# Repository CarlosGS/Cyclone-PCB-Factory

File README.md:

<p align="center">

<div align="center"><i>A 3D-printable (Rep-Rap alike) CNC machine, intended for PCB manufacture.</i></div>
</p>  

Read this, it's important!
-----------

Please note that this project is no longer active and is of historical interest only.
===========

Check out this thread before printing the parts: <https://github.com/CarlosGS/Cyclone-PCB-Factory/issues/57>

**Also take a look at the following locations:**

- **Releases: <https://github.com/carlosgs/Cyclone-PCB-Factory/releases>**
- **Documentation: <https://github.com/carlosgs/Cyclone-PCB-Factory/wiki>**

<p align="center">

<div align="center"><i>Cyclone v2. Picture by bq</i></div>
</p>

Mail list / Forum  
-------------------
If you are interested in this project, please consider joining our mail list:  
**English: <https://groups.google.com/forum/#!forum/cyclone-pcb-factory>**  
**Spanish/Español: <https://groups.google.com/forum/#!forum/cyclone-pcb-factory-es>**  

Links of interest  
====================
- **[GitHub project network](https://github.com/carlosgs/Cyclone-PCB-Factory/network)** (useful to find the latest work by collaborators)
- **[Wiki entry on RepRap.org](http://reprap.org/wiki/Cyclone_PCB_Factory)**
- **[Joco's Cyclone journey in the mail list](https://groups.google.com/forum/#!topic/cyclone-pcb-factory/o_YzXokpLnA)**
- **[A year of development (Jan/2014)](https://web.archive.org/web/20150627040708/http://carlosgs.es/node/47)** (project evolution during 2013)
- **[List of suppliers](https://github.com/carlosgs/Cyclone-PCB-Factory/wiki/List-of-suppliers)**

Getting the (development) source files  
========================================
Install git (http://git-scm.com/) onto your system. Then run a clone:

	git clone git://github.com/carlosgs/Cyclone-PCB-Factory.git

This will download the latest sources into a directory named 'Cyclone-PCB-Factory'.  

Current stable version: 2.1  
--  

**Recent news:**
* [Kris Wauters](http://www.digitalplayground.be/) has designed [a set of feet](http://www.thingiverse.com/thing:1131591) that raise up the machine and allow to place the electronics underneath. He has also made a [Z endstop support](http://www.thingiverse.com/thing:1131591). Check out his beautiful build in [his blog](http://www.digitalplayground.be/?p=3255).
* Introductory tutorial: [**Milling a bowl with bCNC**](https://github.com/carlosgs/grblForCyclone/wiki/2%29-Hello-World!-Mill-a-bowl-with-bCNC) (**implemented support for GRBL firmware in RAMPS and Sanguinololu** 3D printer electronics. GRBL is better for CNCs than Marlin).
* Released [**Cyclone XL (beta)**](Output_files/Cyclone_XL) with a milling area of **500x250mm**.
* BQ additions have been re-incorporated into the main parametric design (zip-ties in the Y carriage linear bearing holders, longer Z motor gear, same orientation for the Y rod idlers).
* If you use RAMPS, you may want to try this [GRBL mod](https://github.com/carlosgs/grblForCyclone), it is better than Marlin. Control it with the [bCNC](https://github.com/vlachoudis/bCNC) graphical interface.
* Z carriage modified for Dremel 3000 by [Nicolas Arias](https://groups.google.com/forum/#!msg/cyclone-pcb-factory/mfZC0KEy7gw/TaSLBKO9QJUJ) and [Marcos Bladauskas](https://groups.google.com/forum/#!msg/cyclone-pcb-factory/WJLWC5qAm-w/70eSQ2DBCAAJ) ([download it here](Output_files/Zcarriages)).
* Check out the [Arduino CNC shield housing](http://www.thingiverse.com/thing:929981) by Oliver Kreuzenbeck (Helicon).
* [Source code improvements (better parameterization, M4 screw version)](https://github.com/carlosgs/Cyclone-PCB-Factory/pull/33) by [Arne Durr (D-Byte)](https://github.com/D-Byte).
* An [**aluminium spindle holder**](https://github.com/carlosgs/Cyclone-PCB-Factory/pull/40) by [Marc Muntada (quikshot)](https://github.com/quikshot) ([download it here](Output_files/Zcarriages)).
* There is also [a folder](bq_additions) with the version by [Pedro de Oro](https://github.com/PedroDeOro) and [Luis Díaz](http://diwo.bq.com/author/ldiaz/) from **bq**, with some additions that simplify the assembly process (these have already been merged into the main branch).
* Daniel Evrard has [assembled Cyclone in Sketchup](https://groups.google.com/forum/#!msg/cyclone-pcb-factory/1TpFxE7avRo/EBSx7ouy9GwJ) which can be very useful as a template.
* Thanks must also go to [ve3sjk](https://github.com/ve3sjk), [joco-nz](https://github.com/joco-nz), Aisflow, Yiannis Mandravellos, Samuel Kranz and [yOPERO](https://github.com/yOPERO) for their constructive discussions and continuous support.
* If your printer is too small to print the main frames of the machine, take a look at the [**shorter version of the frames**](Output_files/ShorterVersion) (thanks [Burt Bicksler!!](https://groups.google.com/forum/#!msg/cyclone-pcb-factory/ue6NiWs713w/A7_4h4Ynf54J)).

**Cyclone PCB Factory V2.0 was developed in the department of innovation and robotics at [bq](http://www.bq.com/)**  
**V2.0** addressed all the issues from the original design, and implementing improvements by yOPERO, Martin Zabojnik and others:  

* More robust design with tougher parts:
 * Better holders for the linear bearings (vibration made them slide away)
 * Reinforced nut/screw holders
* Anti-backlash mechanisms
* Improved gears with smoother edges
* Protective cover for the gears
* Attachment for a vacuum cleaner
* Better scalability (parameterized design)
* Using a [Dremel 200](http://www.dremel.com/en-us/tools/Pages/ToolDetail.aspx?pid=200+Series) as the spindle motor
* Integrated endstop holders

<p align="center">

<div align="center"><i>Render of Cyclone v2.0</i></div>
</p>  

<p align="center">

<div align="center"><i>The new design tries to be more parameterized</i></div>
</p>

Videos  
--  
- October 2015. Full milling process with bCNC, by Carlosgs: <https://www.youtube.com/watch?v=tWrt1B1CeP0>
- September 2015. Cyclone PCB jogging and homing test with bCNC, by Ianmcmill: <https://www.youtube.com/watch?v=GqbSjCq_hWg>
- July 2015. v2.0 Milling a PCB, timelapse by Helicon007: <https://www.youtube.com/watch?v=GpFG2Z8Jt-w>
- April 2015. Cyclone PCB Factory belt drive, by Nihilianth: <https://www.youtube.com/watch?v=bdu1vz6ndGs>
- April 2015. Introduction & assembly tips, by Project23D: <https://www.youtube.com/watch?v=0mW087ijIdE>
- v2.0 Plexiglass "Open Source Hardware" keychain: <http://www.youtube.com/watch?v=3Kftgog89wQ>
- v2.0 Cyclone Logo in PCB (October 2014): <http://www.youtube.com/watch?v=_6oWuco_N8U>
- v2.0a Plexiglass Cyclone logo (August 2014): <http://www.youtube.com/watch?v=lPQlIvBf7Ak>
- v2.0a Milling wax (August 2014): <http://www.youtube.com/watch?v=drV_r_OSsi4>
- February 2014. First drawing test with the Cyclone PCB Factory CNC, by Samuel Ureta: <https://www.youtube.com/watch?v=F7SczbShmxA>
- December 2013. Adjustment of Cyclone PCB Factory Y Stepper Motor Current, by Glen Chung: <https://www.youtube.com/watch?v=-TPqWOsY0Ls>
- v0.9.7 Cyclone PCB factory, the process (June 2013): <http://www.youtube.com/watch?v=fKW3fwy1h0k>
- v0.9.6 Y axis concept by yOPERO <http://www.youtube.com/watch?v=XzcobonQP40>
- v0.9.5 Probing a PCB <http://www.youtube.com/watch?v=m5zXL8k5T9E>
- v0.9.5 Milling MDF <http://www.youtube.com/watch?v=2QpxjheEjEc> and <http://www.youtube.com/watch?v=zjav0hBtmYA>
- v0.8 Drawing test: <http://www.youtube.com/watch?v=Y-HSdE89JOM>
- v0.7.5 XY axis test: <http://www.youtube.com/watch?v=9umlq4oHG64>
- v0.7.5 High speed XY test: <http://www.youtube.com/watch?v=H3uYCXryj60>

- October 2015. Evolution of the Cyclone-PCB-Factory GitHub repository (Gource Visualization), by Landon Wilkins: <https://www.youtube.com/watch?v=0ANaGCHkaco>

More pictures  
--  

License  
--
License: **Attribution - Share Alike - Creative Commons (<http://creativecommons.org/licenses/by-sa/3.0/>)**  

Authors:  
--
**Carlos García Saura (<http://github.com/CarlosGS>)** released the project as open-source and is the current maintainer.

**Many other people keeps contributing to the project (check GitHub contributions and "most active posters" at <https://groups.google.com/forum/#!aboutgroup/cyclone-pcb-factory>).**  

Special thanks  
--  
- **Arne Durr (D-Byte)** finished the OpenScad assembly and made the code much more parametric.  
- Plenty of feedback from **Pedro de Oro**, **Alberto Valero**, **Alberto Mendez** (and **Obijuan**, **Pacle**, **Jesus**, **Ana**, **Santi**, **Antonio**, **Jose**... :-P) at the _department of innovation and robotics at [bq](http://www.bq.com/)_. **Cyclone is much more user-friendly thanks to you!**  
- **Glen Chung** (<https://github.com/glenchung>) improved the OpenScad code quite a lot (a much more elegant code), providing a great start point for V2.0.  
- Z axis concepts by **Quim Borras** and the spindle motor holder by **Misan** were really useful!! Also, **Diego Viejo**'s machine was of great inspiration for the Z axis (<https://plus.google.com/u/0/photos/113930344830086538817/albums/5868944432651911713?authkey=CLDJgdehlN773gE>) **Thank you all!!**  
- This design woudn't have been possible without the encouragement of the **Panda CNC community** (<https://plus.google.com/u/0/communities/102402711800402614517>)  
- Also, thanks to **Juan González-Gómez (Obijuan <http://iearobotics.com>)** for naming the machine Cyclone :)  

Derived from / we have used / inspirational  
--
- "Linear actuator concept for CNC machines" by **Carlosgs** (<http://www.thingiverse.com/thing:45103>)  
- "Obiscad library" by **Obijuan** (<https://github.com/Obijuan/obiscad>)  
- "Minimal footprint friction-fit LM8UU holder" by **thantik** (<http://www.thingiverse.com/thing:23041>)  
- "Spindle mount for ShapeOko" by **Misan** (<http://www.thingiverse.com/thing:26740>)  
- "Carro Z para Cyclone CNC mill intended for PCB" by **Quim** (<http://www.thingiverse.com/thing:80718>)  
- "Write.scad (and DXF fonts)" by **HarlanDMii** (<http://www.thingiverse.com/thing:16193>)  
- "PCB Machining Vise" by **Forgetful_Guy** (<http://www.thingiverse.com/thing:63578>)  

Credit for the ideas used  
--  
The origin of Cyclone took place while I (carlosgs) was inside the **Panda CNC** community (<https://plus.google.com/u/0/communities/102402711800402614517>). This is from December 2012 to mid-February 2013.  
Here is the credit for the ideas that were used:  

* _Let's design a 3D-printable CNC for PCB milling, it will be named Panda:_ **Guillermo Welch** (mid-December, via Google Talk)  
* _X carriage rod distribution:_ **César Augusto Fernández Cano** claims Cyclone's X axis is a derivate of his concept: <https://plus.google.com/u/0/111421387442355054591/posts/QrfYtEuZBaj>  
* _100x160mm workspace:_ **David Martin** <https://dl.dropboxusercontent.com/u/16122275/PandaCNC_credit/workplace_size.png>  
* _Using gears to drive the X-Y axes:_ **Guillermo Welch** <https://plus.google.com/u/0/101232926728463427403/posts/QjZGNcWcgGg>  
* _Regarding the woodbase:_ **Guillermo Welch** always contemplated the possibility of attaching the machine (optionally) to a woodbase. I decided to use the base as a main structural part instead. See <https://dl.dropboxusercontent.com/u/16122275/PandaCNC_credit/woodbase.png> (screenshot from <https://plus.google.com/u/0/113437723819360223498/posts/8LDCSSVWqCS>)  
* _List of CNC endmill types:_ **David Martin** <https://dl.dropboxusercontent.com/u/16122275/PandaCNC_credit/cnc_endmill_types.png>  

Please note I have taken screenshots of the post that are on the closed G+ Panda community (<https://plus.google.com/u/0/communities/116318709564872967169>). You can register and see by yourself.  

**All other development present on Cyclone has nothing to do with Panda and is not related to the Panda project.**  

Disclaimer  
--
This hardware/software is provided "as is", and you use the hardware/software at your own risk. Under no circumstances shall any author be liable for direct, indirect, special, incidental, or consequential damages resulting from the use, misuse, or inability to use this hardware/software, even if the authors have been advised of the possibility of such damages.  

Please cite as:
--
Garcia-Saura, C. (2013). Cyclone PCB Factory. GitHub. https://doi.org/10.5281/ZENODO.10442930

Latex / Bibtex citation:
```bibtex
@misc{cyclonepcb2013,
  author = {Garcia-Saura, Carlos},
  title = {Cyclone PCB Factory},
  publisher = {GitHub},
  year = {2013},
  doi = {10.5281/ZENODO.10442930},
  url = {https://doi.org/10.5281/ZENODO.10442930}
}
```

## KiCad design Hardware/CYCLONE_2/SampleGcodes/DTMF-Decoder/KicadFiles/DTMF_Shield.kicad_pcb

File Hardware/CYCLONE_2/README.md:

A 3D-printable (Rep-Rap alike) CNC machine, intended for PCB manufacture.  

Read this, it's important!
===========================
If you are reading this, then you are looking at the development version of Cyclone PCB Factory.
This means files may present inconsistencies (dimensions mismatch, lack of tolerances, etc).
If you just want to build the machine, take a look at the following locations:

- **Releases: <https://github.com/carlosgs/Cyclone-PCB-Factory/releases>**
- **Documentation: <http://reprap.org/wiki/Cyclone_PCB_Factory>**

<p align="center">

<div align="center"><i>Cyclone v2.0</i></div>
</p>

Mail list / Forum  
-------------------
If you are interested in this project, please consider joining our mail list:  
**<https://groups.google.com/forum/#!forum/cyclone-pcb-factory>**  
Any help and feedback will be appreciated, particularly with software usage and software development :)  

Links of interest  
====================
- **[Project network](https://github.com/carlosgs/Cyclone-PCB-Factory/network)** (useful to find the latest work by collaborators)
- **[Wiki entry on RepRap.org](http://reprap.org/wiki/Cyclone_PCB_Factory)**
- **[A year of development (01/20/2014)](http://carlosgs.es/node/47)** (with information regarding the evolution of the project in 2013)

Getting the (development) source files  
========================================
Install git (http://git-scm.com/) onto your system. Then run a clone:

	git clone git://github.com/carlosgs/Cyclone-PCB-Factory.git

This will download the latest sources into a directory named 'Cyclone-PCB-Factory'.  

Version 2.0  
--  

**Cyclone PCB Factory V2.0 was developed in the department of innovation and robotics at [bq](http://www.bq.com/)**  

V2.0 addresses all the issues from the original design, and implementing improvements by yOPERO, Martin Zabojnik and others.  

* More robust design with tougher parts:
 * Better holders for the linear bearings (vibration made them slide away)
 * Reinforced nut/screw holders
* Anti-backlash mechanisms
* Improved gears with smoother edges
* Protective cover for the gears
* Attachment for a vacuum cleaner
* Better scalability (parametrized design)
* Using a [Dremel 200](http://www.dremel.com/en-us/tools/Pages/ToolDetail.aspx?pid=200+Series) as the spindle motor
* Integrated endstop holders

Future improvements:  
--  
* Endstop integration for Z (integrated probe)
* Re-implement the Z carriage, currently inherited from Cyclone V1

Videos  
--  
- v2.0 Plexiglass "Open Source Hardware" keychain: <http://www.youtube.com/watch?v=3Kftgog89wQ>
- v2.0 Cyclone Logo in PCB (October 2014): <http://www.youtube.com/watch?v=_6oWuco_N8U>
- v2.0a Plexiglass Cyclone logo (August 2014): <http://www.youtube.com/watch?v=lPQlIvBf7Ak>
- v2.0a Milling wax (August 2014): <http://www.youtube.com/watch?v=drV_r_OSsi4>
- v0.9.7 Cyclone PCB factory, the process (June 2013): <http://www.youtube.com/watch?v=fKW3fwy1h0k>
- v0.9.6 Y axis concept by Yopero <http://www.youtube.com/watch?v=XzcobonQP40>  
- v0.9.5 Probing a PCB <http://www.youtube.com/watch?v=m5zXL8k5T9E>  
- v0.9.5 Milling MDF <http://www.youtube.com/watch?v=2QpxjheEjEc> and <http://www.youtube.com/watch?v=zjav0hBtmYA>  
- v0.8 Drawing test: <http://www.youtube.com/watch?v=Y-HSdE89JOM>  
- v0.7.5 XY axis test: <http://www.youtube.com/watch?v=9umlq4oHG64>  
- v0.7.5 High speed XY test: <http://www.youtube.com/watch?v=H3uYCXryj60>  

Bill of materials (obsolete, to be updated and moved to the RepRap wiki page)  
--  
Kobus' <https://docs.google.com/spreadsheet/ccc?key=0AjYcEd1WlkqCdERINEFvRk9mVTZvdXZFR0VHVjRWc2c#gid=0>  
Robsbots' <https://docs.google.com/spreadsheet/ccc?key=0AmiiQRLnjs9cdE12VDFmTHJ4N3JoTzcwbkJPb0ZLSWc#gid=0>  
Carlosgs' <https://docs.google.com/spreadsheet/ccc?key=0AsQp8IK25R4IdGk3LTdOWmpFR0Nrc0RhaVJaUC1CMUE>  

<p align="center">

<div align="center"><i>Render of Cyclone v2.0</i></div>
</p>  

<p align="center">

<div align="center"><i>The new design tries to be more parametrized</i></div>
</p>

License  
--
License: **Attribution - Share Alike - Creative Commons (<http://creativecommons.org/licenses/by-sa/3.0/>)**  

Authors:  
--
Carlos García Saura (Carlosgs <http://carlosgs.es>) is the original author of V2.0.  
Many other people keeps contributing to the project (check "most active posters" at <https://groups.google.com/forum/#!aboutgroup/cyclone-pcb-factory>).  

Special thanks  
--  
- Plenty of feedback from **Pedro de Oro**, **Alberto Valero**, **Alberto Mendez** (and **Obijuan**, **Pacle**, **Jesus**, **Ana**, **Santi**, **Antonio**, **Jose**... :-P) at the _department of innovation and robotics at [bq](http://www.bq.com/)_. **Cyclone is much more user-friendly thanks to you!**
- Z axis concepts by **Quim Borras** and the spindle motor holder by **Misan** were really useful!! Also, **Diego Viejo**'s machine was of great inspiration for the Z axis (<https://plus.google.com/u/0/photos/113930344830086538817/albums/5868944432651911713?authkey=CLDJgdehlN773gE>) **Thank you all!!**  
- This design woudn't have been possible without the encouragement of the **Panda CNC community** (<https://plus.google.com/u/0/communities/102402711800402614517>)  
- Also, thanks to **Juan González-Gómez (Obijuan <http://iearobotics.com>)** for naming the machine Cyclone :)  

Derived from / we have used / inspirational  
--
- "Linear actuator concept for CNC machines" by **Carlosgs** (<http://www.thingiverse.com/thing:45103>)  
- "Obiscad library" by **Obijuan** (<https://github.com/Obijuan/obiscad>)  
- "Minimal footprint friction-fit LM8UU holder" by **thantik** (<http://www.thingiverse.com/thing:23041>)  
- "Spindle mount for ShapeOko" by **Misan** (<http://www.thingiverse.com/thing:26740>)  
- "Carro Z para Cyclone CNC mill intended for PCB" by **Quim** (<http://www.thingiverse.com/thing:80718>)  
- "Write.scad (and DXF fonts)" by **HarlanDMii** (<http://www.thingiverse.com/thing:16193>)  
- "PCB Machining Vise" by **Forgetful_Guy** (<http://www.thingiverse.com/thing:63578>)  

Credit for the ideas used  
--  
The origin of Cyclone took place while I (carlosgs) was inside the **Panda CNC** community (<https://plus.google.com/u/0/communities/102402711800402614517>). This is from December 2012 to mid-February 2013.  
Here is the credit for the ideas that were used:  

* _Let's design a 3D-printable CNC for PCB milling, it will be named Panda:_ **Guillermo Welch** (mid-December, via Google Talk)  
* _X carriage rod distribution:_ **César Augusto Fernández Cano** claims Cyclone's X axis is a derivate of his concept: <https://plus.google.com/u/0/111421387442355054591/posts/QrfYtEuZBaj>  
* _100x160mm workspace:_ **David Martin** <https://dl.dropboxusercontent.com/u/16122275/PandaCNC_credit/workplace_size.png>  
* _Using gears to drive the X-Y axes:_ **Guillermo Welch** <https://plus.google.com/u/0/101232926728463427403/posts/QjZGNcWcgGg>  
* _Regarding the woodbase:_ **Guillermo Welch** always contemplated the possibility of attaching the machine (optionally) to a woodbase. I decided to use the base as a main structural part instead. See <https://dl.dropboxusercontent.com/u/16122275/PandaCNC_credit/woodbase.png> (screenshot from <https://plus.google.com/u/0/113437723819360223498/posts/8LDCSSVWqCS>)  
* _List of CNC endmill types:_ **David Martin** <https://dl.dropboxusercontent.com/u/16122275/PandaCNC_credit/cnc_endmill_types.png>  

Please note I have taken screenshots of the post that are on the closed G+ Panda community (<https://plus.google.com/u/0/communities/116318709564872967169>). You can register and see by yourself.  

**All other development present on Cyclone has nothing to do with Panda and is not related to the Panda project.**  

Disclaimer  
--
This hardware/software is provided "as is", and you use the hardware/software at your own risk. Under no circumstances shall any author be liable for direct, indirect, special, incidental, or consequential damages resulting from the use, misuse, or inability to use this hardware/software, even if the authors have been advised of the possibility of such damages.

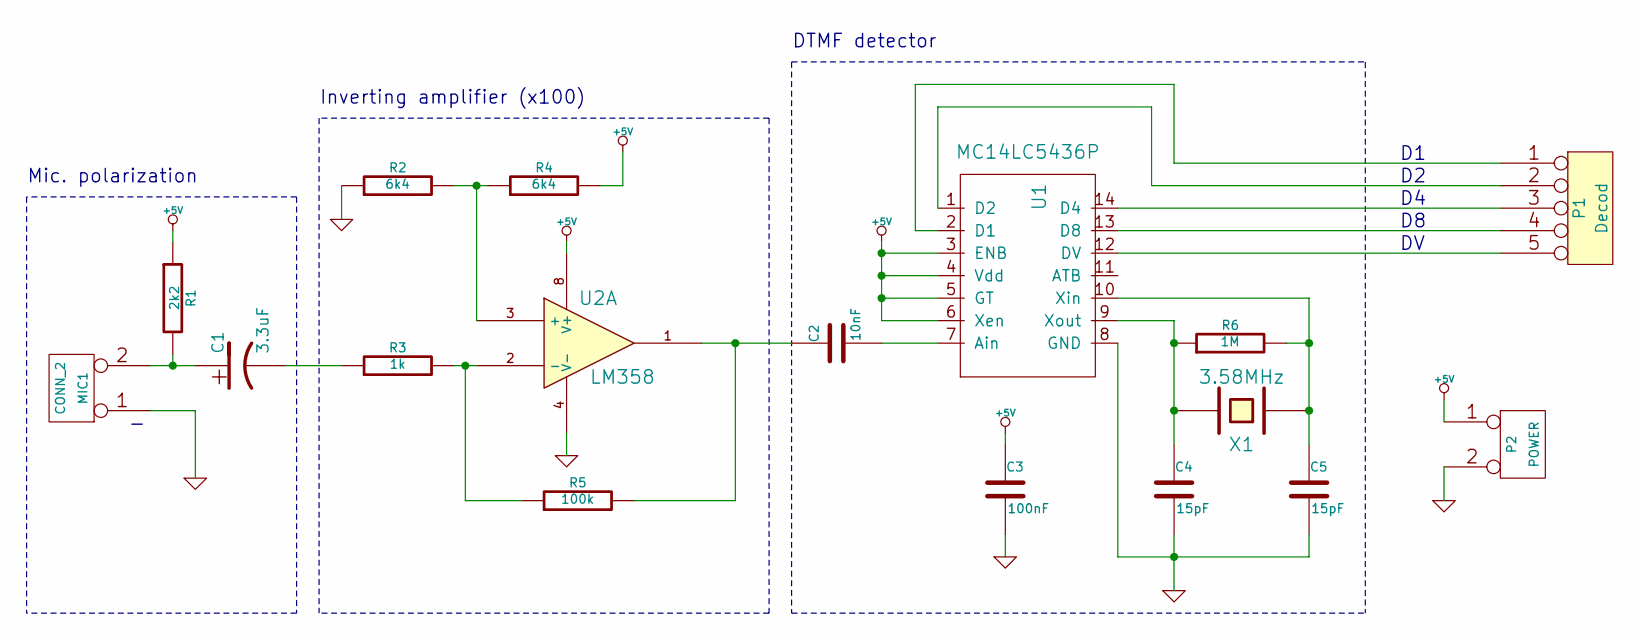
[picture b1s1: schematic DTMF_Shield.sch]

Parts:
C1: 3.3uF
C2: 10nF
C3: 100nF
C4, C5: 15pF
MIC1: CONN_2
P1: Decod
P2: POWER
R1: 2k2
R2, R4: 6k4
R3: 1k
R5: 100k
R6: 1M
U1: MC14LC5436P
U2: LM358
X1: 3.58MHz

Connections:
+5V: C3.1, P2.1, R1.1, R4.2, U1.3 (ENB), U1.4 (Vdd), U1.5 (GT), U1.6 (Xen), U2.8 (V+)
GND: C3.2, C4.2, C5.2, MIC1.1, P2.2 (PM), R2.1, U1.8 (GND), U2.4 (V-)
unnamed: C5.1, R6.2, U1.10 (Xin), X1.1
unnamed: C2.1, R5.2, U2.1
unnamed: R3.2, R5.1, U2.2 (-)
unnamed: C4.1, R6.1, U1.9 (Xout), X1.2
unnamed: C2.2, U1.7 (Ain)
unnamed: P1.4, U1.13 (D8)
unnamed: P1.1, U1.2 (D1)
unnamed: P1.2, U1.1 (D2)
unnamed: P1.3, U1.14 (D4)
unnamed: P1.5, U1.12 (DV)
unnamed: R2.2, R4.1, U2.3 (+)
unnamed: C1.1, MIC1.2 (PM), R1.2
unnamed: C1.2, R3.1

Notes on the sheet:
Inverting amplifier (x100)
Mic. polarization
DTMF detector

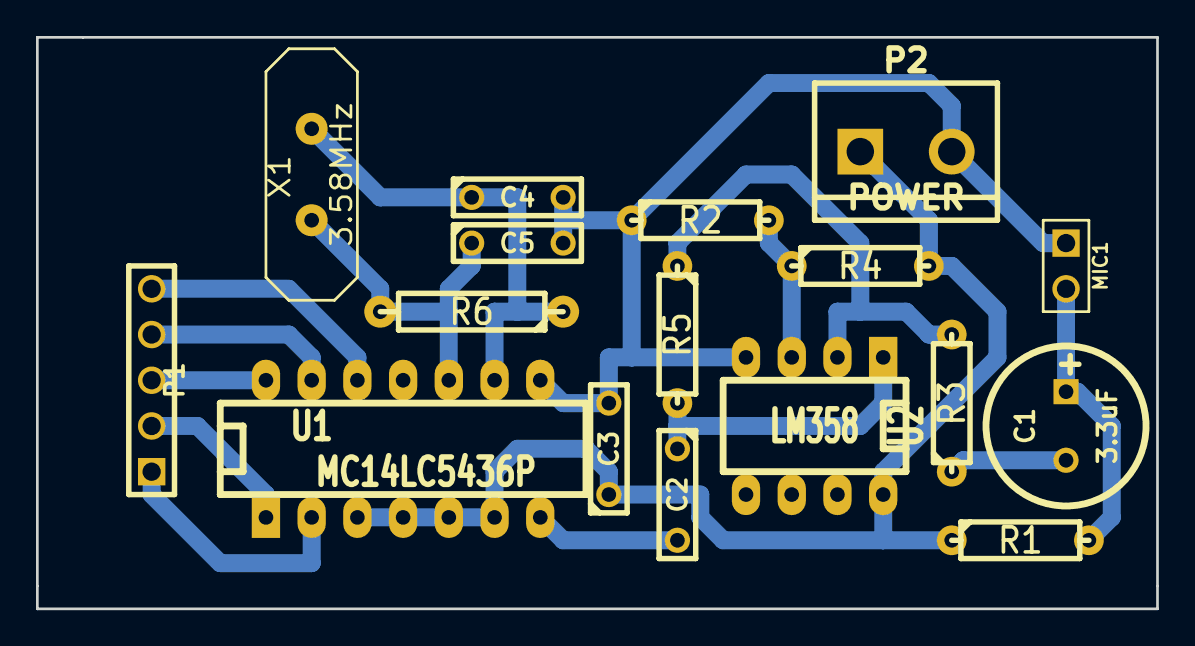
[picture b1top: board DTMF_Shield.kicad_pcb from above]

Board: 2 copper layers, 62.2 x 31.7 mm, 17 parts (0 on the bottom side), 15 nets.

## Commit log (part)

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2013-09-18 Removed Z probe command
2013-09-21 X nut holder update
2013-09-25 Tests compiling Replath
2013-09-26 Re-structuration of the repository, updated readme files for each section
2013-09-26 Added improvements by Harry Binnema: better gears and symmetric Z carriage
2013-09-26 Repository re-organisation
2013-09-27 X carriage nut holder
    //Creating this commit after Carlos re-structuring the git
    X Carriage nut holder covering the whole nut , horizontal and vertical
    screws used for fastening it to the main X carriage body.
2013-09-27 Y rod idler + logo
    Y rod idler redesign to use only one screw and 2 on the sides.
    Logo added as an option to give Cyclone an identity.
    Logo is added as *.dxf file that is extruded into the final design,
    located ad ../libs/logo
2013-09-27 Added Rob's electronics
2013-09-30 Electronics box
    Arduino uno
    cnc shield
    fan
2013-10-01 Adjustment to cncbox
2013-10-04 Updated Rob's electronics to vA0.3
2013-10-10 code refactoring for better adjusting wood base dimension
2013-10-10 code refactoring for better adjusting final X smooth/threaded rod length
2013-10-10 display work bed dimension
2013-10-10 add 150x100x1.5mm PCB board for size checking
2013-10-12 naming cyclone_rod_gear module
2013-10-12 naming cyclone_motor_gear module
2013-10-13 Original Nema17 dimension from MCAD
2013-10-13 Stepper dimension from my BOM
2013-10-13 spindle motor length from my BOM
2013-10-14 adding X stepper and gears
2013-10-14 Y micro switch
2013-10-15 screws for micro switch assembly
2013-10-16 1. move M3 x 8mm grub screw to motor_gear.scad 2. more comments 3. BlackPaint micro switch
2013-10-16 Y micro switch assembly was wrong
2013-10-16 X motor dimension from my BOM
2013-10-16 four of M3 x 8mm to mount X motor
2013-10-16 six of 2.9 x 16mm self tapping screws for both frames
2013-10-16 2.9 x 13 mm was a little too short, use 2.9 x 16 mm instead
2013-10-16 add Y smooth rod fix
2013-10-16 add Y smooth rod fix add self tapping screw 2.9 x 16 mm
2013-10-17 exploded drawing might be useful. disabled by default
2013-10-18 add X rod gear, bearing, nut
2013-10-19 Endstop Holder by NewtonrRob from http://www.thingiverse.com/thing:30085
2013-10-19 add micro switchs for X and Y
2013-10-19 add self tapping screw for attaching linear bearing holder to work bed
2013-10-19 increase X_Wood_Base for case design revise a comment
2013-10-20 add Z rod gear
2013-10-20 fine tune smooth rod and threaded rod length of X and Y axes
2013-10-20 Fixed crlf issue of *.scad files
2013-10-20 code refactoring
2013-10-20 bolts and nuts to attach z_carriage top and bottom
2013-10-20 Added Glen's renders
2013-10-21 fix "Non-Plastic Parts" for machine base, work bed, smooth rod, and thread rod.
2013-10-21 add a M8 nut and two screws for Y_nut_holder
2013-10-22 fix compile WARNING: Ignoring unknown variable 'length'.
2013-10-22 fix compile WARNING: Imported file (../libs/Write/orbitron.dxf) found in document root instead of relative to the importing module. This behavior is deprecated
2013-10-22 non plastic parts for X_carriage
2013-10-22 add PCB Machining Vise (http://www.thingiverse.com/thing:63578) to hold PCB board
2013-10-23 fix redundant message
2013-10-23 Updated Glen's renders
2013-10-27 fix X End_Stop_Holder and re-position both PCB_vise_1s to accomandate X travel reduced by X End_Stop_Holder
2013-10-27 update renders
2013-11-04 Added CSG file
2013-11-07 add template_workbed_top.dxf
2014-01-16 stopping gits
2014-01-16 EXPLAINING
2014-01-16 Tiding before sending commit my build to the "Development" folder
2014-01-16 Tiding up before sending it to "Development" folder.
2014-01-17 initial a.txt
2014-01-17 initial b.txt
2014-01-17 Loading yOPERO'S latest built
2014-01-18 A fake Spindle that holds a pen to draw pcb board instead of milling
    working video: http://youtu.be/mdT-6VdgRn0
2014-01-19 Adding CNC_shieldBox files
2014-01-23 Deleted CSG file that wasn't necessary
2014-01-23 Added description to the Spindle Pen by Glen Chung
2014-01-23 Added simple template
2014-01-23 Deleted Release folder
2014-01-23 Fixed image paths
2014-01-23 Updated software list
2014-01-23 Moved python scripts to its own folder
2014-01-23 Added logo files
2014-01-23 Added more space between the motor shaft and the nuts
2014-01-23 Updated Z motor gear stl file
2014-01-23 Updated readme format
2014-01-23 Removed unnecessary title when linking images
2014-06-17 Added parts for vacuum cleaner attachment (work in progress)
2014-07-01 Added files for the new iteration (work in progress)
2014-07-08 Improved animation functions
2014-07-10 Added MCAD library as submodule
2014-07-10 Merged Y rod idlers into Y frames source
2014-07-10 Increased OpenScad default fragment resolution
2014-07-10 Created Y rod idlers
2014-07-16 Added X frames
2014-07-17 Added GIF animation
2014-07-18 Added Y threaded rod stand. Reduced frame thickness
2014-07-20 Work on the Y nut holder
2014-07-21 Deleted temporary files
2014-07-21 Updated templates
2014-07-22 Added submodule information to readme
2014-07-22 Added README to the new version
2014-07-22 Linked GIF animation
2014-07-22 Added Y nut holder
2014-07-22 Added generation of Y carriage DXF
2014-07-23 Added workbed DXF generation. Updated anti-backlash part measures
2014-07-24 Finished the Y linear bearing holders
2014-07-24 Updated render
2014-07-24 Added DXFs
2014-07-25 Improved linear bearing holder. Work on the XZ axis
2014-07-28 Work on the XZ carriages
2014-07-28 Generated STLs and plate
2014-08-04 Modified X carriage
2014-08-04 Added X nut holder
2014-08-05 Added note regarding OpenScad default parameters, added PCB holder (work in progress)
2014-08-06 Fixed X carriage
2014-08-07 Imrpoved PCB holder, updated renders, added sample gerber and gcodes
2014-08-07 Updated animation
2014-08-11 Added Heekscad tests
2014-08-18 Incorporated arduino MEGA screws in the base
2014-08-18 Added electronic board shape
2014-08-18 Added truncation to motor gear
2014-08-19 Improved gears
2014-08-20 Updated gears, work in the X gear cover
2014-08-25 Updated vacuum cleaner attachment, added sample gcode
2014-08-28 Updated Y carriage parts (better endstop integration, softer linear bearing holders). Integrated X endstop in X right frame
2014-08-29 Work on the X carriage, updated PCB holder STL
2014-09-01 Updated README with 2.0 and development information
2014-09-01 Updated shorter frames, updated Readme and template names
2014-09-02 Increased M8 rod tolerance, renamed files for easier identification
2014-09-02 Tuned tolerances, renamed files
2014-09-06 Added endstop bumper to X carriage
2014-09-08 Updated X carriage with anti-backlash spring system
2014-09-09 Added screw holder to X gear cover
2014-09-10 Finished X gears cover
2014-09-11 Finished gear covers. Identical for both axis
2014-09-11 Render comparison
2014-09-11 Finished XY gear covers
2014-09-11 Updated frames: Rotated motor 5deg, added wire slots, added crocodile clip holders
2014-09-12 Improved X frames
2014-09-15 Finished PCB holder vise
2014-09-15 Improved color representation, Z carriage imported to improve 3D representation
2014-09-16 Updated renders
2014-09-16 Added detachable part
2014-09-17 Renamed STLs, shorter names
2014-09-17 Updated file names
2014-09-22 Added M8 keychain scad source file
2014-09-22 Added FlatCAM default settings
2014-11-04 Rename folders
2014-11-05 Fixed README image paths
2014-11-05 Included a copy of the required libraries
2014-11-05 Moved libraries into source code folder
2014-11-05 Modified the description of the inherited parts
2014-11-05 Abbreviated source files name
2014-11-05 Moved logos into source folder
2014-11-05 Renamed folder to dxf
2014-11-05 Removed unnecessary dxf files
2014-11-29 Added proper screw cap values
    Fixed the TODO: proper screw cap values
    Based on: http://www.roymech.co.uk/Useful_Tables/Screws/cap_screws.htm
    Diameter is pulled from the table METRIC_BOLT_CAP_DIAMETERS and the cap height is the metric size of the bold.
2014-11-29 Fixed bolt size issue
    Bolt size of the pcb holder could not be chanced. Now it can
2014-11-29 StepperMotor mount fix
    StepperMotor mount dint render
2014-11-29 Kept larger tolerances
2014-11-30 Add support for rendering gears
    Used a modified file from the inherited_files/XYgears folder
2014-11-30 Add support for rendering gears
    Added cyclone_rod_gear and cyclone_motor_gear modules
2014-11-30 Add support for rendering gears
    Replaced the gear mock-ups with real gears
2014-12-01 Fix for wrong left/right frame render
    fix for issue https://github.com/carlosgs/Cyclone-PCB-Factory/issues/27
2014-12-06 Update for Z carriage rendering
2014-12-06 Update for Z carriage rendering
    Small update for the z carriage motor gear
2014-12-07 Gears fix and improvement
2014-12-07 Added configs/Default_config.h
    Added configs/Default_config.h to make it easy to chance parameters like
    screw size and tolerances
2014-12-08 Removed files from previous iteration
2014-12-08 Removed sample Gcodes folder
2014-12-08 Added pictures
2014-12-08 Updated Readme and added pictures
2014-12-08 Added output for the new layout
2014-12-08 Merged remote-tracking branch 'master/master'
2014-12-09 Added 2 more screw and nuts
    added screw and nuts to the y nut holder and fixed a hight error for the
    pcb holder screws
2014-12-09 Position render fix and little code cleanup
2014-12-09 Update to the base template
2014-12-09 Added support for an alternitive z-carriage
2014-12-29 Parameterized tolerances for the gears
2014-12-29 Added SVG source file
2015-01-21 Increased nut tolerance
2015-02-04 Fixed tolerances
2015-02-17 Added tool selection from config file. Added parametrized SpindelHolderAttach option for Z_Carriage
2015-02-23 Fixed folder name and README
2015-02-23 Removing duplicate folders
2015-02-28 Fixed small render issue
2015-02-28 Deleted old image
2015-02-28 Updated Readme for 2.1
2015-06-12 Added L/R letters to left&right frames for easy identification
2015-09-14 Linked Dremel 3000 Z carriage, and GRBL shield 3D printed enclosure
2015-09-14 Linked GRBL for ramps
2015-09-25 Separated gears so they can render independently
2015-09-25 Elongated Z motor gear
2015-09-25 Added bq improvements to linear bearing holders
2015-09-26 Updated assembled model
2015-09-26 Re-rendered gears (longer Z motor gear), Y linear bearing holders (zip-ties and nut support), Y rod idlers (corrected L/R), and Z carriage (additional screw holes)
2015-09-26 Re-arranged STL to simplify printing
2015-09-26 Linked firmware repositories
2015-09-26 Rounded base corners
2015-09-26 First version
2015-09-26 Added Cyclone XL, and moved Z carriages into separate folder
2015-09-26 Removed obsolete FreeCAD file
2015-09-26 updated header
2015-09-26 Release of Cyclone XL
2015-09-29 Cleaned up readme
2015-09-30 Linked bCNC tutorial
2015-09-30 Added images of Y axis assembly by bq
2015-09-30 Merged images
2015-09-30 Changed format to jpg
2015-09-30 Added X axis pictures
2015-09-30 Fixed picture
2015-10-01 Added readme
2015-10-13 Added assembly tip (picture by Pablo2048)
2015-11-19 Linked work by Kris Wauters and videos
2015-12-15 Repair XY gear cover
2015-12-15 Repair Xcarriage
2015-12-15 Repair xRightFrame
2015-12-15 YBackFrame
2015-12-15 Repair YCarriage Linear Bearing Holder
2015-12-15 Repair Y Carriage Nut Holder
2015-12-15 Y Front Rod Idlers
2015-12-15 Z Carriage Dremel 200
2015-12-16 Repair Rod Fixer
2015-12-16 Repair Vacuume cleaner attachment
2015-12-16 Repaired short frames
2016-02-17 Fixes tolerance for Z-axis gears.
2016-08-28 Create Cyclopea (Cyclone with spindles)
2016-08-30 No son definitivos
2017-08-22 Add warning about tolerances mismatch
2017-09-01 Generated new STLs for gears after tolerance fix

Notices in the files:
Hardware/CYCLONE_2/SampleGcodes/DTMF-Decoder/KicadFiles/DTMF_Shield.kicad_pcb:
License: CC-BY-SA
